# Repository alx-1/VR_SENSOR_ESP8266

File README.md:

# VR_SENSOR_ESP8266
 Send and receive sensor data over WiFI via UDP for the ES8266 (Lolin Wemos D1)
 
 TODO :
 0. forma para agregar las infos del usuario (medida)
 1. Decidir que tipo de información presentar a los usuarios durante la calibración
 2. Auto-calibración del sensor (rutina en arduino)
 3. Représentation des données en courbes
 4. Enviar datos de los tres sensores

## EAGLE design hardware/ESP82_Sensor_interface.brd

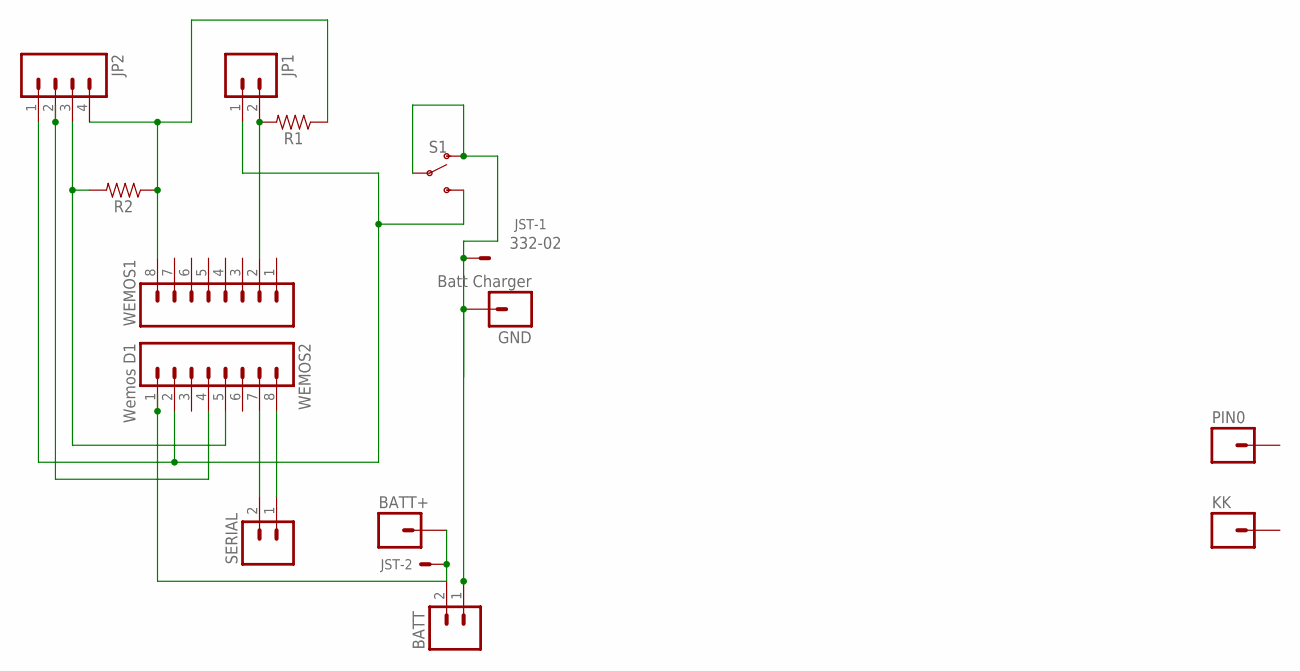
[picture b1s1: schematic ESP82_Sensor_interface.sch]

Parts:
BATT: M02LOCK_LONGPADS; 1X02_LOCK_LONGPADS
BATT+: M01PTH; 1X01
GND: Batt Charger; 1X01
JP1: M02PTH; 1X02
JP2: M04PTH; 1X04
JST: 332-02
KK: M01PTH; 1X01
PIN0: M01PTH; 1X01
R1, R2: 1206
S1: SWITCH-SPDT-SMD-RIGHT-ANGLE; SWITCH_SPST_SMD_A
SERIAL: M02PTH; 1X02
WEMOS1: M08; 1X08_ROUND
WEMOS2: Wemos D1; 1X08_ROUND

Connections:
3.3V: JP2.4, R1.1, R2.1, WEMOS1.8
5V: BATT.2, BATT+.1, JST.2, WEMOS2.1
A0: JP1.2, R1.2, WEMOS1.2
D2: JP2.3, R2.2, WEMOS2.5
ENTREEGND: BATT.1, GND.1, JST.1, S1.1 (O), S1.2
GND: JP1.1, JP2.1, S1.3 (S), WEMOS2.2
unnamed: JP2.2, WEMOS2.4
RX: SERIAL.2, WEMOS2.7
TX: SERIAL.1, WEMOS2.8

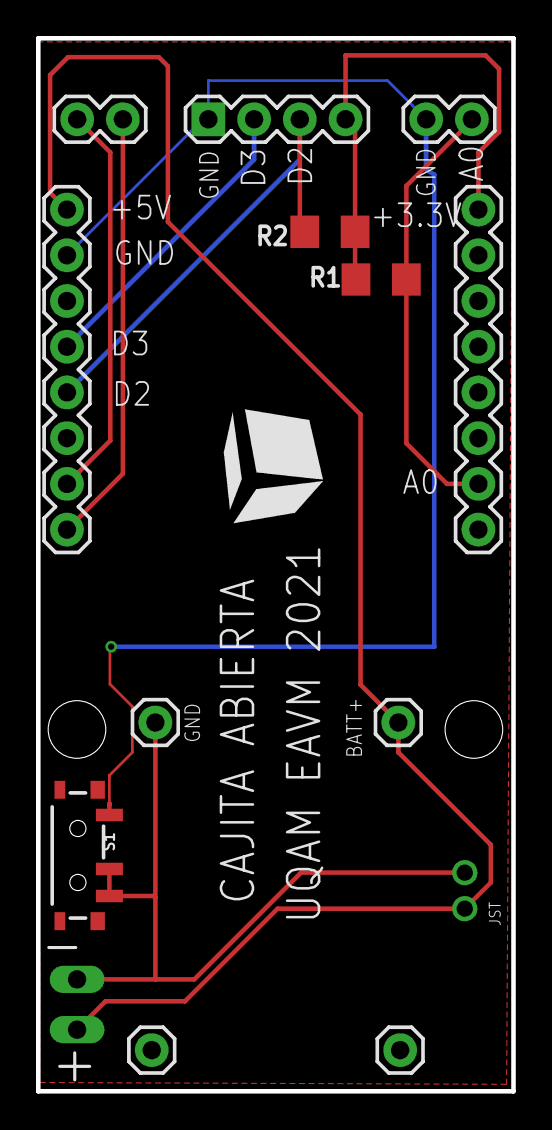
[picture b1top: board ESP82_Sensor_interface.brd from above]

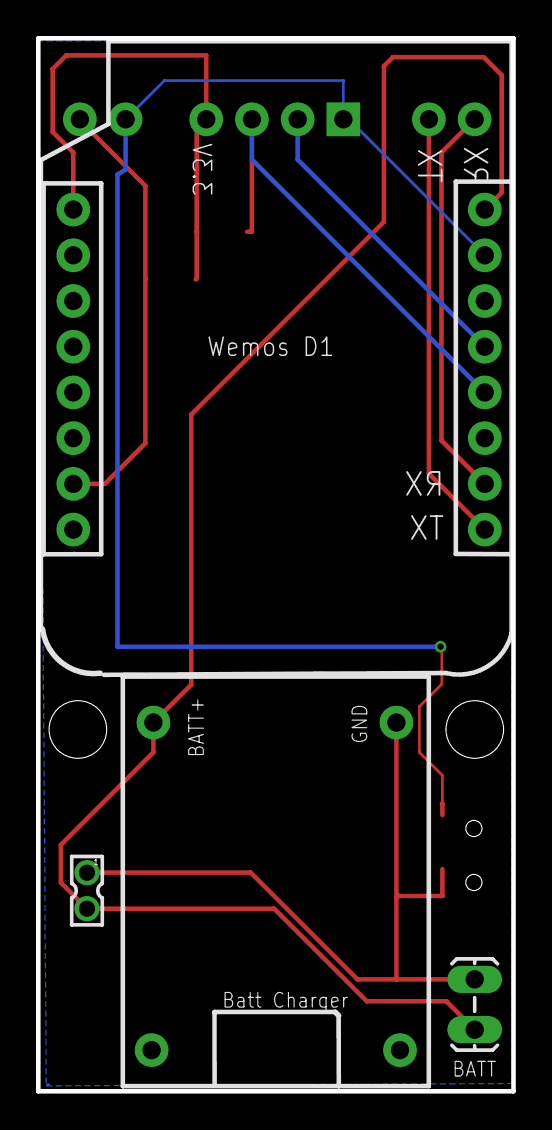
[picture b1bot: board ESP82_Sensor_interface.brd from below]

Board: 2 copper layers, 26.4 x 58.5 mm, 16 parts (2 on the bottom side), 9 nets.

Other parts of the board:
U$1, U$2: M3-HOLE

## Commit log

2021-05-04 Server + Client files
    Have yet to test with actual sensor and need the receiver code to interface to Unity
2021-05-25 Cambios para enviar una 'string' a Unity
2021-06-03 plaquetas para la versión ESP8266
2021-06-03 img de la plaqueta
2021-08-10 revolution avec plaquette
2021-08-17 new hardware version
2021-09-12 New board
    updated image
2021-09-15 New board

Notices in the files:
parts and their libraries:
SparkFun-Connectors: Licensing: Creative Commons ShareAlike 4.0 International - https://creativecommons.org/licenses/by-sa/4.0
